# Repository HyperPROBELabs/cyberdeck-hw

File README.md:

# cyberdeck-hw

Hardware design repository for the Cyberdeck platform
by **Kali Assistant** — HyperPROBE Labs

---

## Overview

This repository contains the **hardware design files** for the Cyberdeck project, including:

* PCB schematics and layouts
* mechanical CAD models
* fabrication and manufacturing data
* supporting hardware resources

The goal is to provide a **modular, reproducible, and hackable hardware platform** for embedded systems, networking, and cybersecurity applications.

---

## Usage

You are free to:

* study the design
* modify and improve it
* manufacture and sell derived hardware
* integrate it into your own systems

Please review the license terms below before use.

---

## Licensing

Unless otherwise specified, this repository is licensed as follows:

### Hardware

All hardware design files are licensed under the
CERN Open Hardware Licence Version 2 - Permissive.

---

### Documentation

All documentation (e.g., manuals, images, diagrams) is licensed under the
Creative Commons Attribution 4.0 International.

---

### Subdirectory Overrides

If a subdirectory contains its own license file or license header:

> **That license takes precedence for files within that subdirectory.**

---

## Attribution

When redistributing or using this work, please attribute:

Kali Assistant

HyperPROBE Labs

---

## Contributing

Contributions are welcome, including:

* hardware improvements
* PCB optimization
* mechanical refinements
* documentation updates

Please ensure:

* proper attribution is maintained
* SPDX license identifiers are included where applicable

---

## Disclaimer

This hardware is provided **"AS IS"**, without warranty of any kind.
Use at your own risk.

---

## Notes

* This is an evolving hardware platform
* Designs may change between revisions
* Not all files are guaranteed to be production-ready

---

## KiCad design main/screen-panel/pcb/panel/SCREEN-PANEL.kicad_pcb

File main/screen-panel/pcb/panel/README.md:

# Screen Panel PCB

This directory contains the PCB design and layout files for the Cyberdeck **screen panel module**.

---

## Status

**April 29, 2026**
Design and prototyping in progress.

---

## Directory Structure

```
./production/
├── GERBER-*.zip   # Manufacturing files for PCB fabrication
├── BOM-*.csv      # Bill of Materials
└── CPL-*.csv      # Component Placement List (Pick & Place)

./panel-pcb-model*.step.xz  # Compressed 3D STEP model of the PCB
```

---

## 3D Model Usage

Due to GitHub file size limits, the PCB 3D model is compressed using `xz`.

To extract:

```bash
xz -dk panel-pcb-model.step.xz
```

You can then import the `.step` file into your CAD software.

---

## Design Overview

### 50-Pin FPC Integration

The PCB integrates both the camera interface and the Raspberry Pi Touch Display v2 through a **combined 50-pin FPC (Flexible Printed Cable)**.

* FPC design is currently in progress
* Intended to reduce cabling complexity between modules

---

### USB Hub Integration

The board includes a **USB2422 USB hub**, enabling expansion capabilities for the panel.

Two onboard USB expansion module slots are provided for future customization.

---

### Camera Module

Sourcing standalone CMOS sensors is difficult, so the current approach is:

* Use the **Raspberry Pi Camera Module v3 (NoIR)**
* Remove (de-solder) the CMOS module
* Integrate it into this custom PCB design

The camera base and mounting design are still under development.

---

### USB Expansion Modules

Two optional USB-connected addon module slots are included.

Potential use cases:

* Small OLED or TFT displays
* Status indicator LEDs
* Buttons or control interfaces

These modules connect to the onboard USB hub and communicate back to the Cyberdeck motherboard via the 50-pin FPC.

---

## Notes

* This is an actively evolving design
* Hardware, pinout, and module layout may change during prototyping
* Contributions and ideas for USB expansion modules are welcome

---

Cyberdeck Project
Designed by Kali Assistant

Copyright (c) 2026 HyperPROBE Labs. All Rights Reserved.

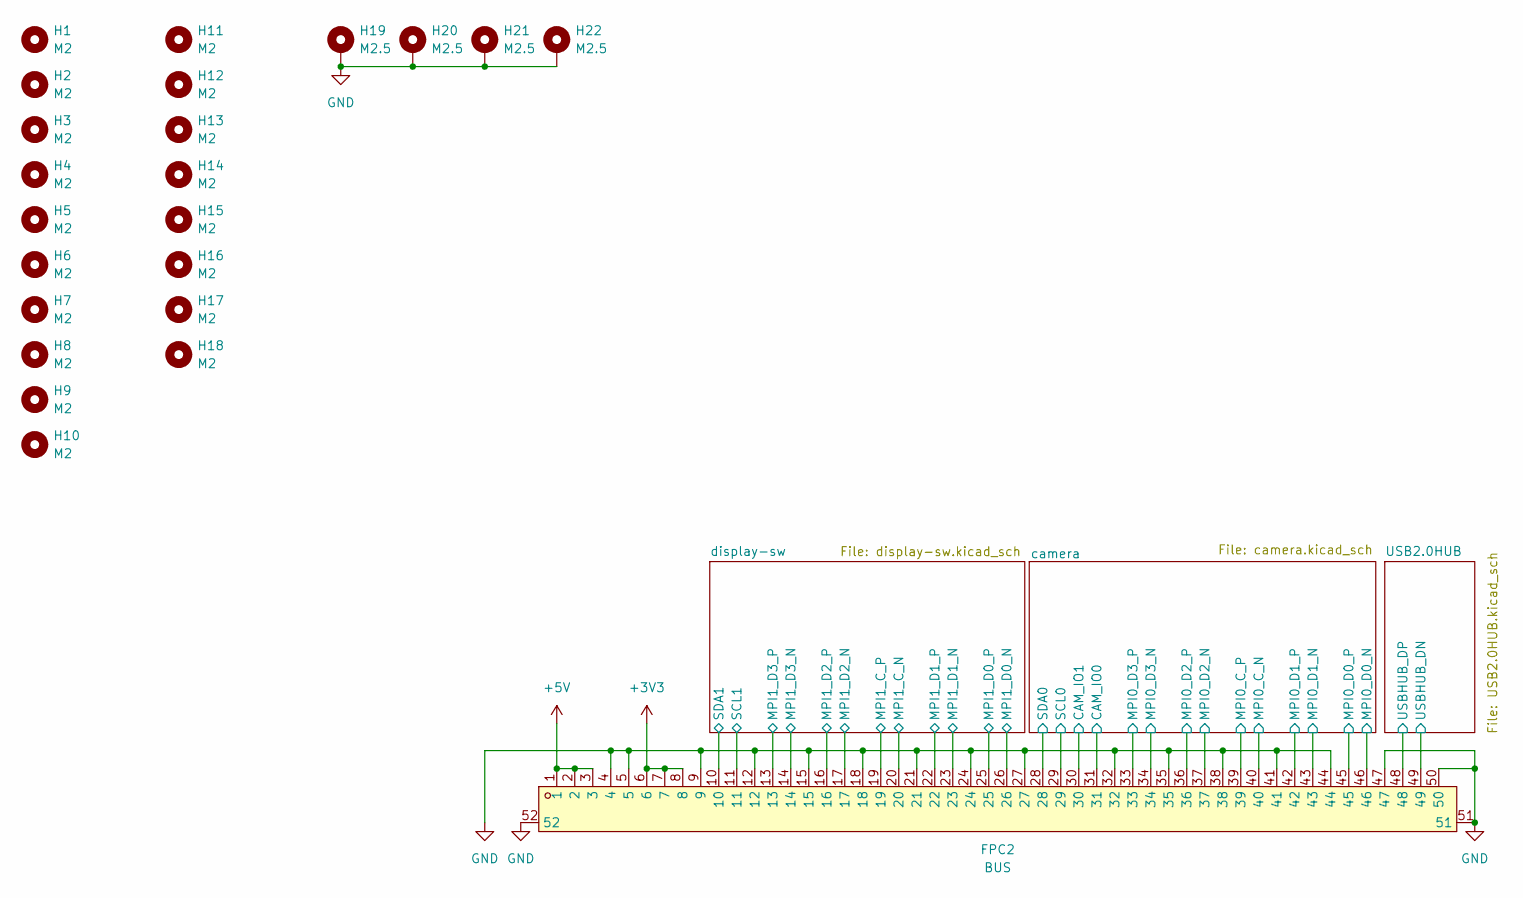
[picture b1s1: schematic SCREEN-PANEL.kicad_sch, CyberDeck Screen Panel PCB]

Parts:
FPC2: BUS; FPC-SMD_50P-P0.50_FH34SRJ-50S-0.5SH; MPN FH34SRJ-50S-0.5SH(50); LCSC Part C3169104
H1, H2, H3, H4, H5, H6, H7, H8, H9, H10, H11, H12, H13, H14, H15, H16, H17, H18: M2; MountingHole_2.2mm_M2_ISO14580
H19, H20, H21, H22: M2.5; MountingHole_2.7mm_M2.5_ISO14580_Pad

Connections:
+3V3: FPC2.6, FPC2.7, FPC2.8; also elsewhere on the board
+5V: FPC2.1, FPC2.2, FPC2.3; also elsewhere on the board
/USB2.0HUB/USBHUB_DN: FPC2.49; also elsewhere on the board
/USB2.0HUB/USBHUB_DP: FPC2.48; also elsewhere on the board
/camera/CAM_IO0: FPC2.31; also elsewhere on the board
/camera/CAM_IO1: FPC2.30; also elsewhere on the board
/camera/MPI0_C_N: FPC2.40; also elsewhere on the board
/camera/MPI0_C_P: FPC2.39; also elsewhere on the board
/camera/MPI0_D0_N: FPC2.46; also elsewhere on the board
/camera/MPI0_D0_P: FPC2.45; also elsewhere on the board
/camera/MPI0_D1_N: FPC2.43; also elsewhere on the board
/camera/MPI0_D1_P: FPC2.42; also elsewhere on the board
/camera/MPI0_D2_N: FPC2.37; also elsewhere on the board
/camera/MPI0_D2_P: FPC2.36; also elsewhere on the board
/camera/MPI0_D3_N: FPC2.34; also elsewhere on the board
/camera/MPI0_D3_P: FPC2.33; also elsewhere on the board
/camera/SCL0: FPC2.29; also elsewhere on the board
/camera/SDA0: FPC2.28; also elsewhere on the board
/display-sw/MPI1_C_N: FPC2.20; also elsewhere on the board
/display-sw/MPI1_C_P: FPC2.19; also elsewhere on the board
/display-sw/MPI1_D0_N: FPC2.26; also elsewhere on the board
/display-sw/MPI1_D0_P: FPC2.25; also elsewhere on the board
/display-sw/MPI1_D1_N: FPC2.23; also elsewhere on the board
/display-sw/MPI1_D1_P: FPC2.22; also elsewhere on the board
/display-sw/MPI1_D2_N: FPC2.17; also elsewhere on the board
/display-sw/MPI1_D2_P: FPC2.16; also elsewhere on the board
/display-sw/MPI1_D3_N: FPC2.14; also elsewhere on the board
/display-sw/MPI1_D3_P: FPC2.13; also elsewhere on the board
/display-sw/SCL1: FPC2.11; also elsewhere on the board
/display-sw/SDA1: FPC2.10; also elsewhere on the board
GND: FPC2.4, FPC2.5, FPC2.9, FPC2.12, FPC2.15, FPC2.18, FPC2.21, FPC2.24, FPC2.27, FPC2.32, FPC2.35, FPC2.38, FPC2.41, FPC2.44, FPC2.47, FPC2.50, FPC2.51, FPC2.52, H19.1 (1_1), H20.1 (1_1), H21.1 (1_1), H22.1 (1_1); also elsewhere on the board

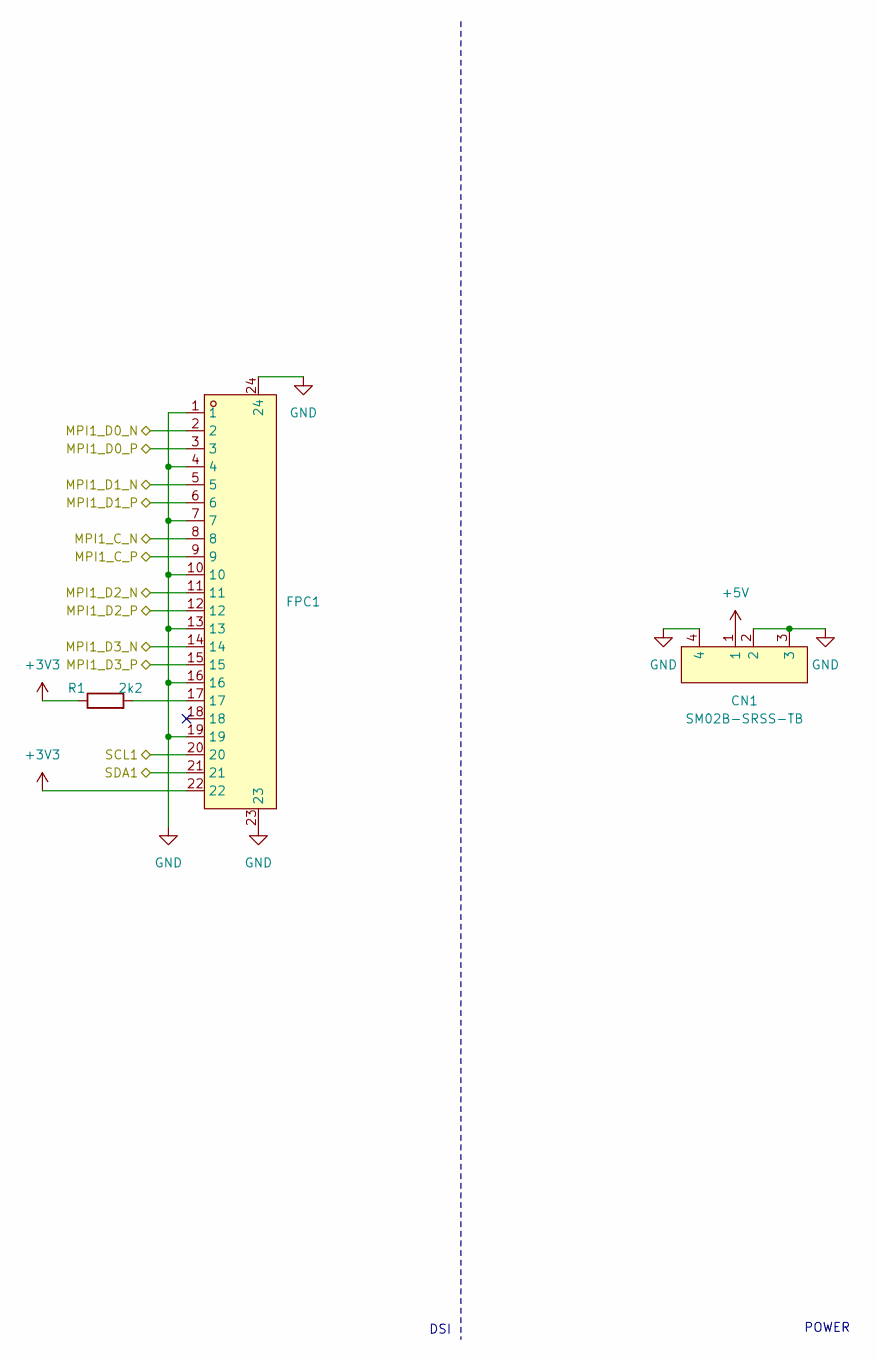
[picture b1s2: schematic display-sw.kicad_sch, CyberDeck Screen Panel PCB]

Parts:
CN1: SM02B-SRSS-TB; CONN-SMD_2P-P1.00_SM02B-SRSS-TB-LF-SN; MPN SM02B-SRSS-TB(LF)(SN); LCSC Part C160402
FPC1: FFC-SMD_22P-P0.50_HRS_FH34SRJ-22S-0.5SH; MPN FH34SRJ-22S-0.5SH(50); LCSC Part C2889325
R1: 2k2; R_0402_1005Metric

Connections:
+3V3: FPC1.22, R1.1; also elsewhere on the board
+5V: CN1.1; also elsewhere on the board
/display-sw/MPI1_C_N: FPC1.8; also elsewhere on the board
/display-sw/MPI1_C_P: FPC1.9; also elsewhere on the board
/display-sw/MPI1_D0_N: FPC1.2; also elsewhere on the board
/display-sw/MPI1_D0_P: FPC1.3; also elsewhere on the board
/display-sw/MPI1_D1_N: FPC1.5; also elsewhere on the board
/display-sw/MPI1_D1_P: FPC1.6; also elsewhere on the board
/display-sw/MPI1_D2_N: FPC1.11; also elsewhere on the board
/display-sw/MPI1_D2_P: FPC1.12; also elsewhere on the board
/display-sw/MPI1_D3_N: FPC1.14; also elsewhere on the board
/display-sw/MPI1_D3_P: FPC1.15; also elsewhere on the board
/display-sw/SCL1: FPC1.20; also elsewhere on the board
/display-sw/SDA1: FPC1.21; also elsewhere on the board
GND: CN1.2, CN1.3, CN1.4, FPC1.1, FPC1.4, FPC1.7, FPC1.10, FPC1.13, FPC1.16, FPC1.19, FPC1.23, FPC1.24; also elsewhere on the board
unnamed: FPC1.17, R1.2

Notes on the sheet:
DSI
POWER

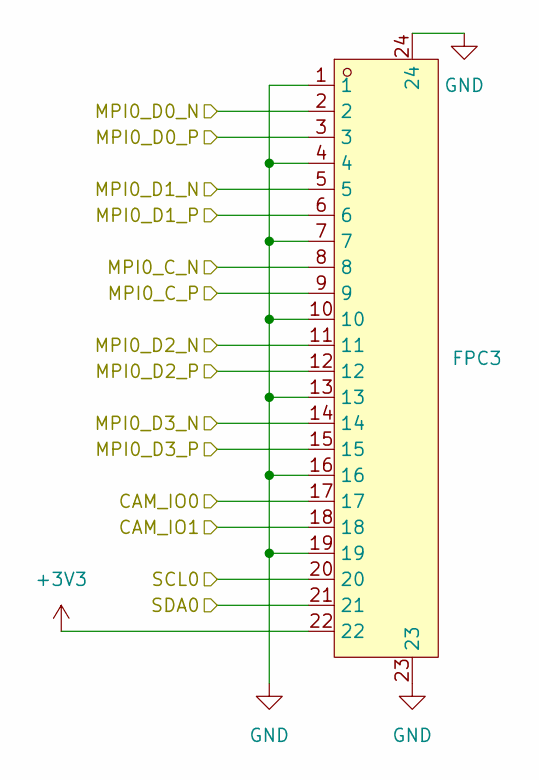
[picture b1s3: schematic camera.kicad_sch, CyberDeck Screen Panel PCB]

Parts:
FPC3: FFC-SMD_22P-P0.50_HRS_FH34SRJ-22S-0.5SH; MPN FH34SRJ-22S-0.5SH(50); LCSC Part C2889325

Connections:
+3V3: FPC3.22; also elsewhere on the board
/camera/CAM_IO0: FPC3.17; also elsewhere on the board
/camera/CAM_IO1: FPC3.18; also elsewhere on the board
/camera/MPI0_C_N: FPC3.8; also elsewhere on the board
/camera/MPI0_C_P: FPC3.9; also elsewhere on the board
/camera/MPI0_D0_N: FPC3.2; also elsewhere on the board
/camera/MPI0_D0_P: FPC3.3; also elsewhere on the board
/camera/MPI0_D1_N: FPC3.5; also elsewhere on the board
/camera/MPI0_D1_P: FPC3.6; also elsewhere on the board
/camera/MPI0_D2_N: FPC3.11; also elsewhere on the board
/camera/MPI0_D2_P: FPC3.12; also elsewhere on the board
/camera/MPI0_D3_N: FPC3.14; also elsewhere on the board
/camera/MPI0_D3_P: FPC3.15; also elsewhere on the board
/camera/SCL0: FPC3.20; also elsewhere on the board
/camera/SDA0: FPC3.21; also elsewhere on the board
GND: FPC3.1, FPC3.4, FPC3.7, FPC3.10, FPC3.13, FPC3.16, FPC3.19, FPC3.23, FPC3.24; also elsewhere on the board

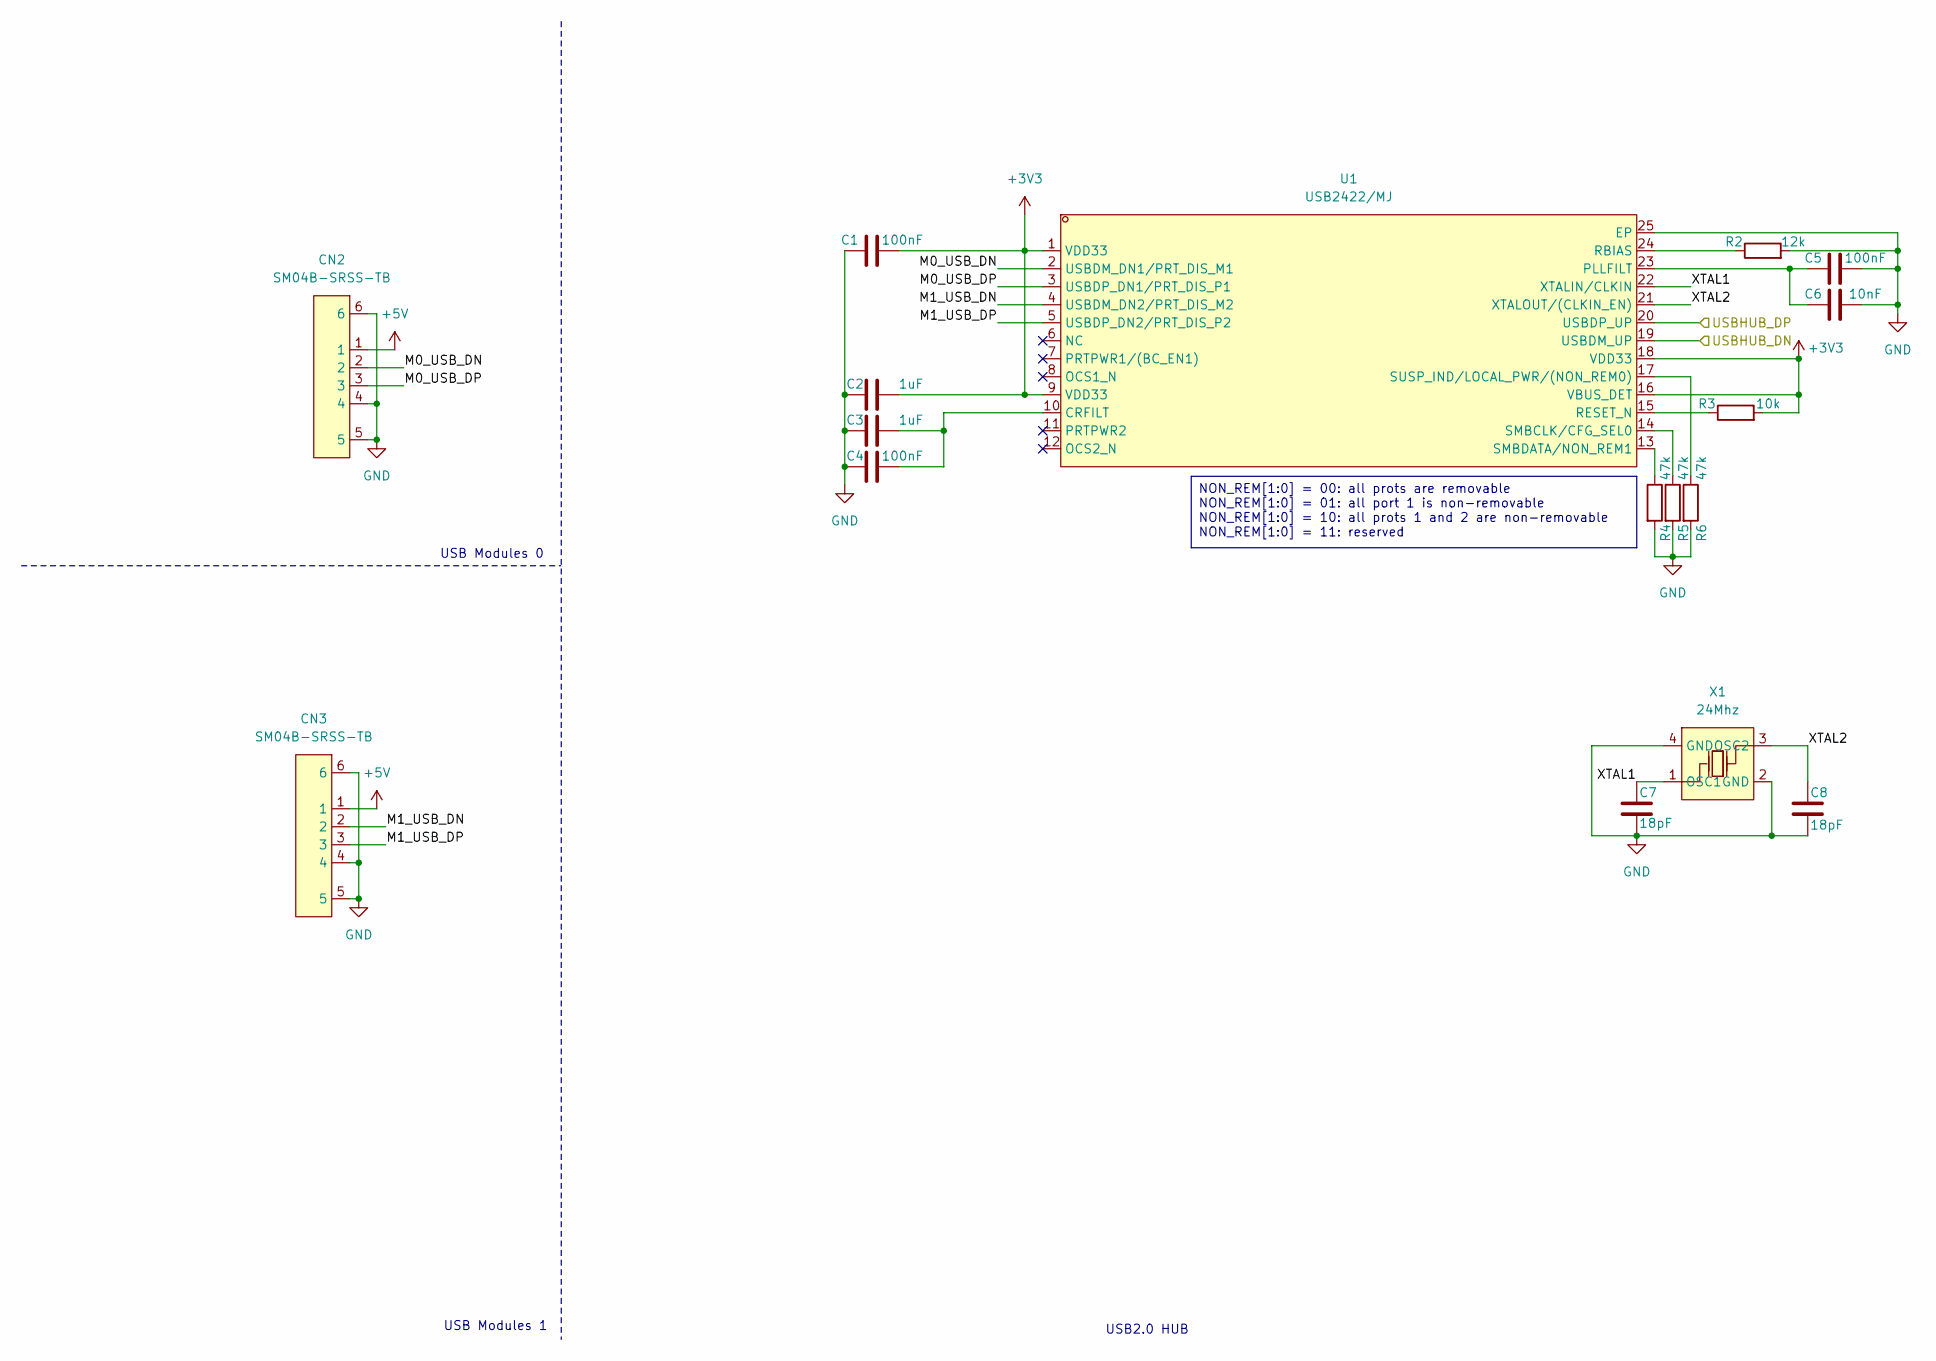
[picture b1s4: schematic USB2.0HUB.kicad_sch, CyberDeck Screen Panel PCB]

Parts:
C1, C4, C5: 100nF; C_0402_1005Metric
C2, C3: 1uF; C_0603_1608Metric
C6: 10nF; C_0402_1005Metric
C7, C8: 18pF; C_0402_1005Metric
CN2, CN3: SM04B-SRSS-TB; CONN-SMD_4P-P1.00_SM04B-SRSS-TB-LF-SN; MPN SM04B-SRSS-TB(LF)(SN); LCSC Part C160404
R2: 12k; R_0402_1005Metric
R3: 10k; R_0402_1005Metric
R4, R5, R6: 47k; R_0402_1005Metric
U1: USB2422/MJ; QFN-24_L4.0-W4.0-P0.50-BL-EP2.6; MPN USB2422/MJ; LCSC Part C633330
X1: 24Mhz; CRYSTAL-SMD_4P-L2.0-W1.6-BL; MPN Q22FA12800489; LCSC Part C255882

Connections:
+3V3: C1.2, C2.2, R3.2, U1.1 (VDD33), U1.9 (VDD33), U1.16 (VBUS_DET), U1.18 (VDD33); also elsewhere on the board
+5V: CN2.1, CN3.1; also elsewhere on the board
/USB2.0HUB/M0_USB_DN: CN2.2, U1.2 (USBDM_DN1/PRT_DIS_M1)
/USB2.0HUB/M0_USB_DP: CN2.3, U1.3 (USBDP_DN1/PRT_DIS_P1)
/USB2.0HUB/M1_USB_DN: CN3.2, U1.4 (USBDM_DN2/PRT_DIS_M2)
/USB2.0HUB/M1_USB_DP: CN3.3, U1.5 (USBDP_DN2/PRT_DIS_P2)
/USB2.0HUB/USBHUB_DN: U1.19 (USBDM_UP); also elsewhere on the board
/USB2.0HUB/USBHUB_DP: U1.20 (USBDP_UP); also elsewhere on the board
/USB2.0HUB/XTAL1: C7.1, U1.22 (XTALIN/CLKIN), X1.1 (OSC1)
/USB2.0HUB/XTAL2: C8.1, U1.21 (XTALOUT/(CLKIN_EN)), X1.3 (OSC2)
GND: C1.1, C2.1, C3.1, C4.1, C5.2, C6.2, C7.2, C8.2, CN2.4, CN2.5, CN2.6, CN3.4, CN3.5, CN3.6, R2.2, R4.2, R5.2, R6.2, U1.25 (EP), X1.2 (GND), X1.4 (GND); also elsewhere on the board
unnamed: C3.2, C4.2, U1.10 (CRFILT)
unnamed: C5.1, C6.1, U1.23 (PLLFILT)
unnamed: R2.1, U1.24 (RBIAS)
unnamed: R3.1, U1.15 (RESET_N)
unnamed: R5.1, U1.14 (SMBCLK/CFG_SEL0)
unnamed: R4.1, U1.13 (SMBDATA/NON_REM1)
unnamed: R6.1, U1.17 (SUSP_IND/LOCAL_PWR/(NON_REM0))

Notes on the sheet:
USB2.0 HUB
USB Modules 1
USB Modules 0
NON_REM[1:0] = 00: all prots are removable NON_REM[1:0] = 01: all port 1 is non-removable NON_REM[1:0] = 10: all prots 1 and 2 are non-removable NON_REM[1:0] = 11: reserved

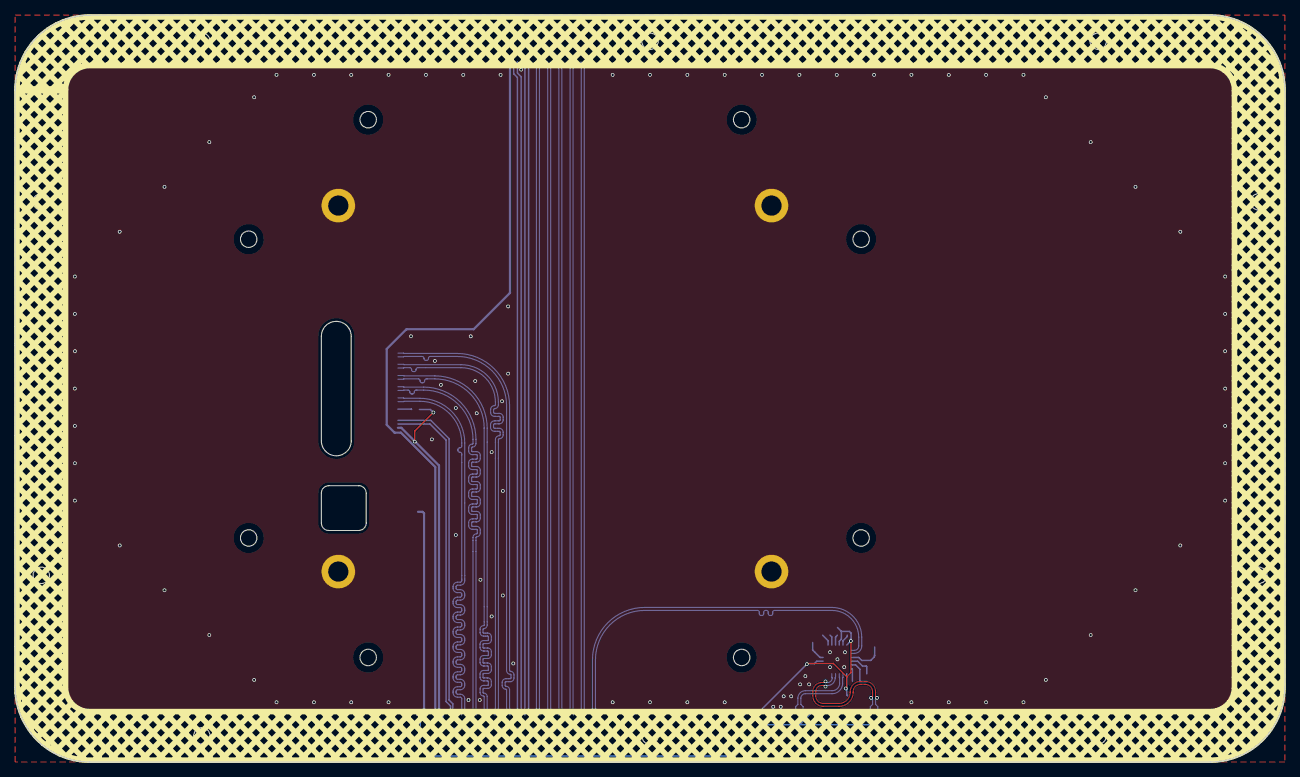
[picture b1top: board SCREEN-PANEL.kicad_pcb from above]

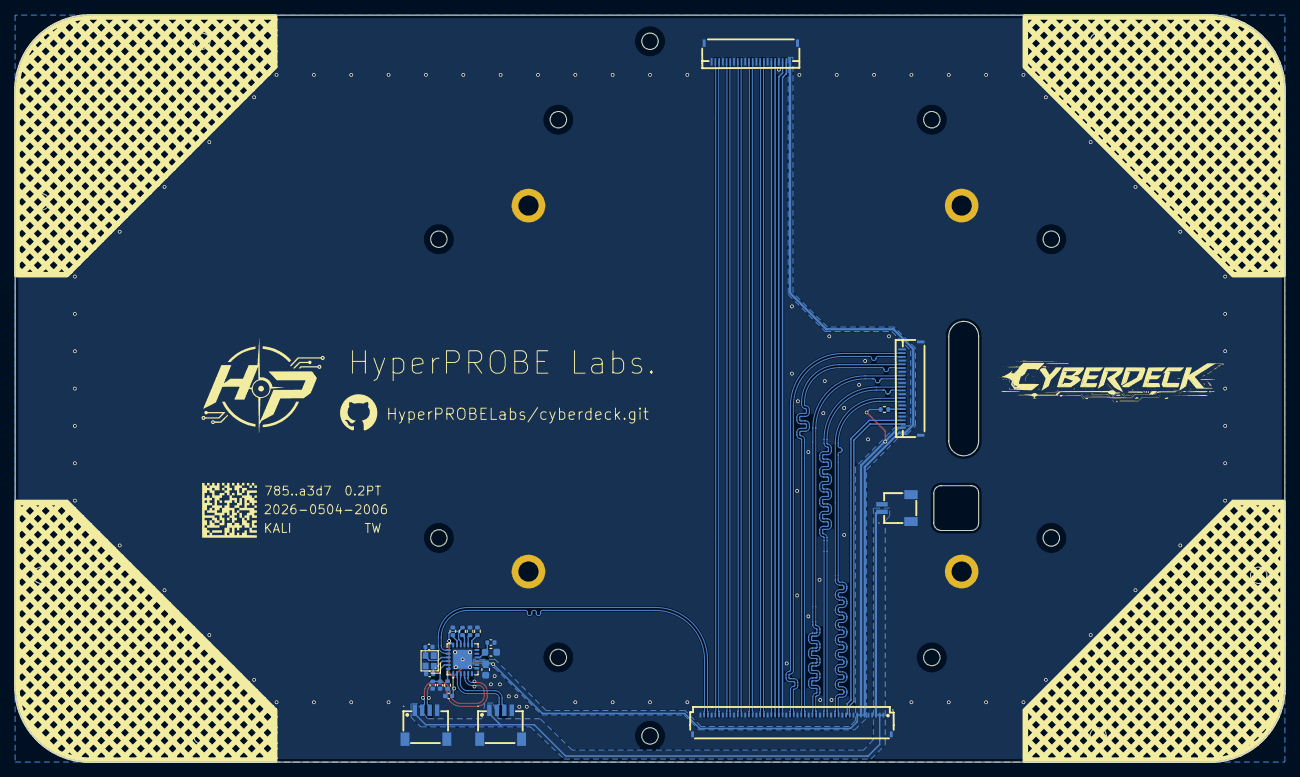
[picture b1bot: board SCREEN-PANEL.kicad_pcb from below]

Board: 2 copper layers, 170.0 x 100.0 mm, 44 parts (22 on the bottom side), 45 nets.

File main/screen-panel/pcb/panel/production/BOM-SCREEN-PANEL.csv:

Comment,Designator,Footprint,LCSC,Quantity
100nF,"C1,C4,C5",C_0402_1005Metric,C437421,3
10k,R3,R_0402_1005Metric,C71617,1
10nF,C6,C_0402_1005Metric,C85973,1
12k,R2,R_0402_1005Metric,C481938,1
18pF,"C7,C8",C_0402_1005Metric,C161176,2
1uF,"C2,C3",C_0603_1608Metric,C77386,2
24Mhz,X1,CRYSTAL-SMD_4P-L2.0-W1.6-BL,C255882,1
2k2,R1,R_0402_1005Metric,C82680,1
47k,"R4,R5,R6",R_0402_1005Metric,C482184,3
BUS,FPC2,FPC-SMD_50P-P0.50_FH34SRJ-50S-0.5SH,C3169104,1
SM02B-SRSS-TB,CN1,CONN-SMD_2P-P1.00_SM02B-SRSS-TB-LF-SN,C160402,1
SM04B-SRSS-TB,"CN2,CN3",CONN-SMD_4P-P1.00_SM04B-SRSS-TB-LF-SN,C160404,2
USB2422/MJ,U1,QFN-24_L4.0-W4.0-P0.50-BL-EP2.6,C633330,1
~,"FPC1,FPC3",FFC-SMD_22P-P0.50_HRS_FH34SRJ-22S-0.5SH,C2889325,2

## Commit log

2026-04-22 add the screen-panel-support-rod design and production files
2026-04-22 BOM item inc.
2026-04-23 BOM No. remane
2026-04-24 README and License
2026-04-27 add the screen panel msin design and production files
2026-04-29 add screen panel pcb design and production files
2026-04-30 update step models
2026-05-04 rerouted the screen panel pairs
